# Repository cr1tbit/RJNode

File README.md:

# RJNode

ESP32-C3 Ethernet relay node (2 relays, CH390D Ethernet).

> [!WARNING]
> **This board runs on 230 V AC mains, which can kill.** Mains voltage is present on the
> input terminal, both fuses, the MOV, the AC/DC module primary, the relays and all output
> terminals whenever the board is connected, even with both relays OFF.
>
> - Only a qualified electrician, or someone competent to work on mains, should build, install or service it.
> - Disconnect and isolate the supply, and verify it is dead, before touching the board or the wiring.
> - Never operate it on mains without the enclosure fitted. Do not touch the PCB, USB-C or
>   programming header while mains is connected. For firmware work, power it from USB only, with mains disconnected.
> - This design has **not been certified or safety-tested**. Its AC/DC module
>   (HLK-5M05) gives only about basic insulation; the RJ45 magnetics are an informal second barrier.
>   It is meant for internal or trial use, inside a closed enclosure, behind a circuit breaker.
>
> You build and use this design at your own risk.

## Power rating

**Proposed rating (not yet validated on hardware): 230 V~ 50 Hz, max 250 W per channel, 500 W total.**

| Parameter | Value |
| --- | --- |
| Supply | 230 V AC, 50 Hz (the AC/DC module accepts 85–264 V AC) |
| Load per channel | ≤ 250 W (≈ 1.2 A at PF 0.9) |
| Total input current | ≤ 2.4 A (main fuse: T4A, 1500 A breaking) |
| LED drivers | ≤ 4 per channel, cold-start inrush ≤ 50 A / 250 µs each |
| Outputs | 2 × changeover (NO/NC), neutral passes through. No PE on the PCB; join PE outside the board |
| Insulation class | Class II (no protective earth) |
| Device consumption | ≤ 5 W (5 V / 1 A AC/DC module) |

Notes:

- **The limit is set by the fuse and the inrush, not by the relays or terminals.** The SRD relays are
  10 A parts derated to about 5 A resistive, and the terminals are rated 16 A / 300 V. The main
  fuse sizing and the inrush budget only cover the figures above. Do not fit a larger fuse to
  get more power.
- **Inrush depends on the number of drivers, not on wattage.** Check each LED driver's datasheet
  against the inrush limit. Cheap drivers without an NTC can exceed it.
- **The firmware never switches both relays at the same instant** (≥ 100 ms apart), so the main fuse sees only one channel's inrush at a time.
- **Large motors, compressors and capacitive loads are not covered** by this rating.
- **Still to verify:** a full-load thermal run (terminal, trace and fuse temperatures inside the
  closed enclosure) and an inrush measurement with the real load.

## Repository layout

| Path | Contents |
| --- | --- |
| `RJNode.kicad_*` | KiCad project: schematic, PCB, custom design rules (`.kicad_dru`) |
| `RJNode-schematic.pdf` | Schematic export |
| `tools/` | KiCad helper scripts (net classes + DRU rules, 3D model assignment) |
| `jlcpcb/` | Fabrication output (gerbers, BOM, CPL) |
| `fw/` | PlatformIO / ESP-IDF firmware — see [fw/README.md](fw/README.md) |
| `3d/` | Enclosure CAD, exports and generators — see [3d/README.md](3d/README.md) |

Regenerate the schematic PDF:

```sh
kicad-cli sch export pdf -o RJNode-schematic.pdf RJNode.kicad_sch
```

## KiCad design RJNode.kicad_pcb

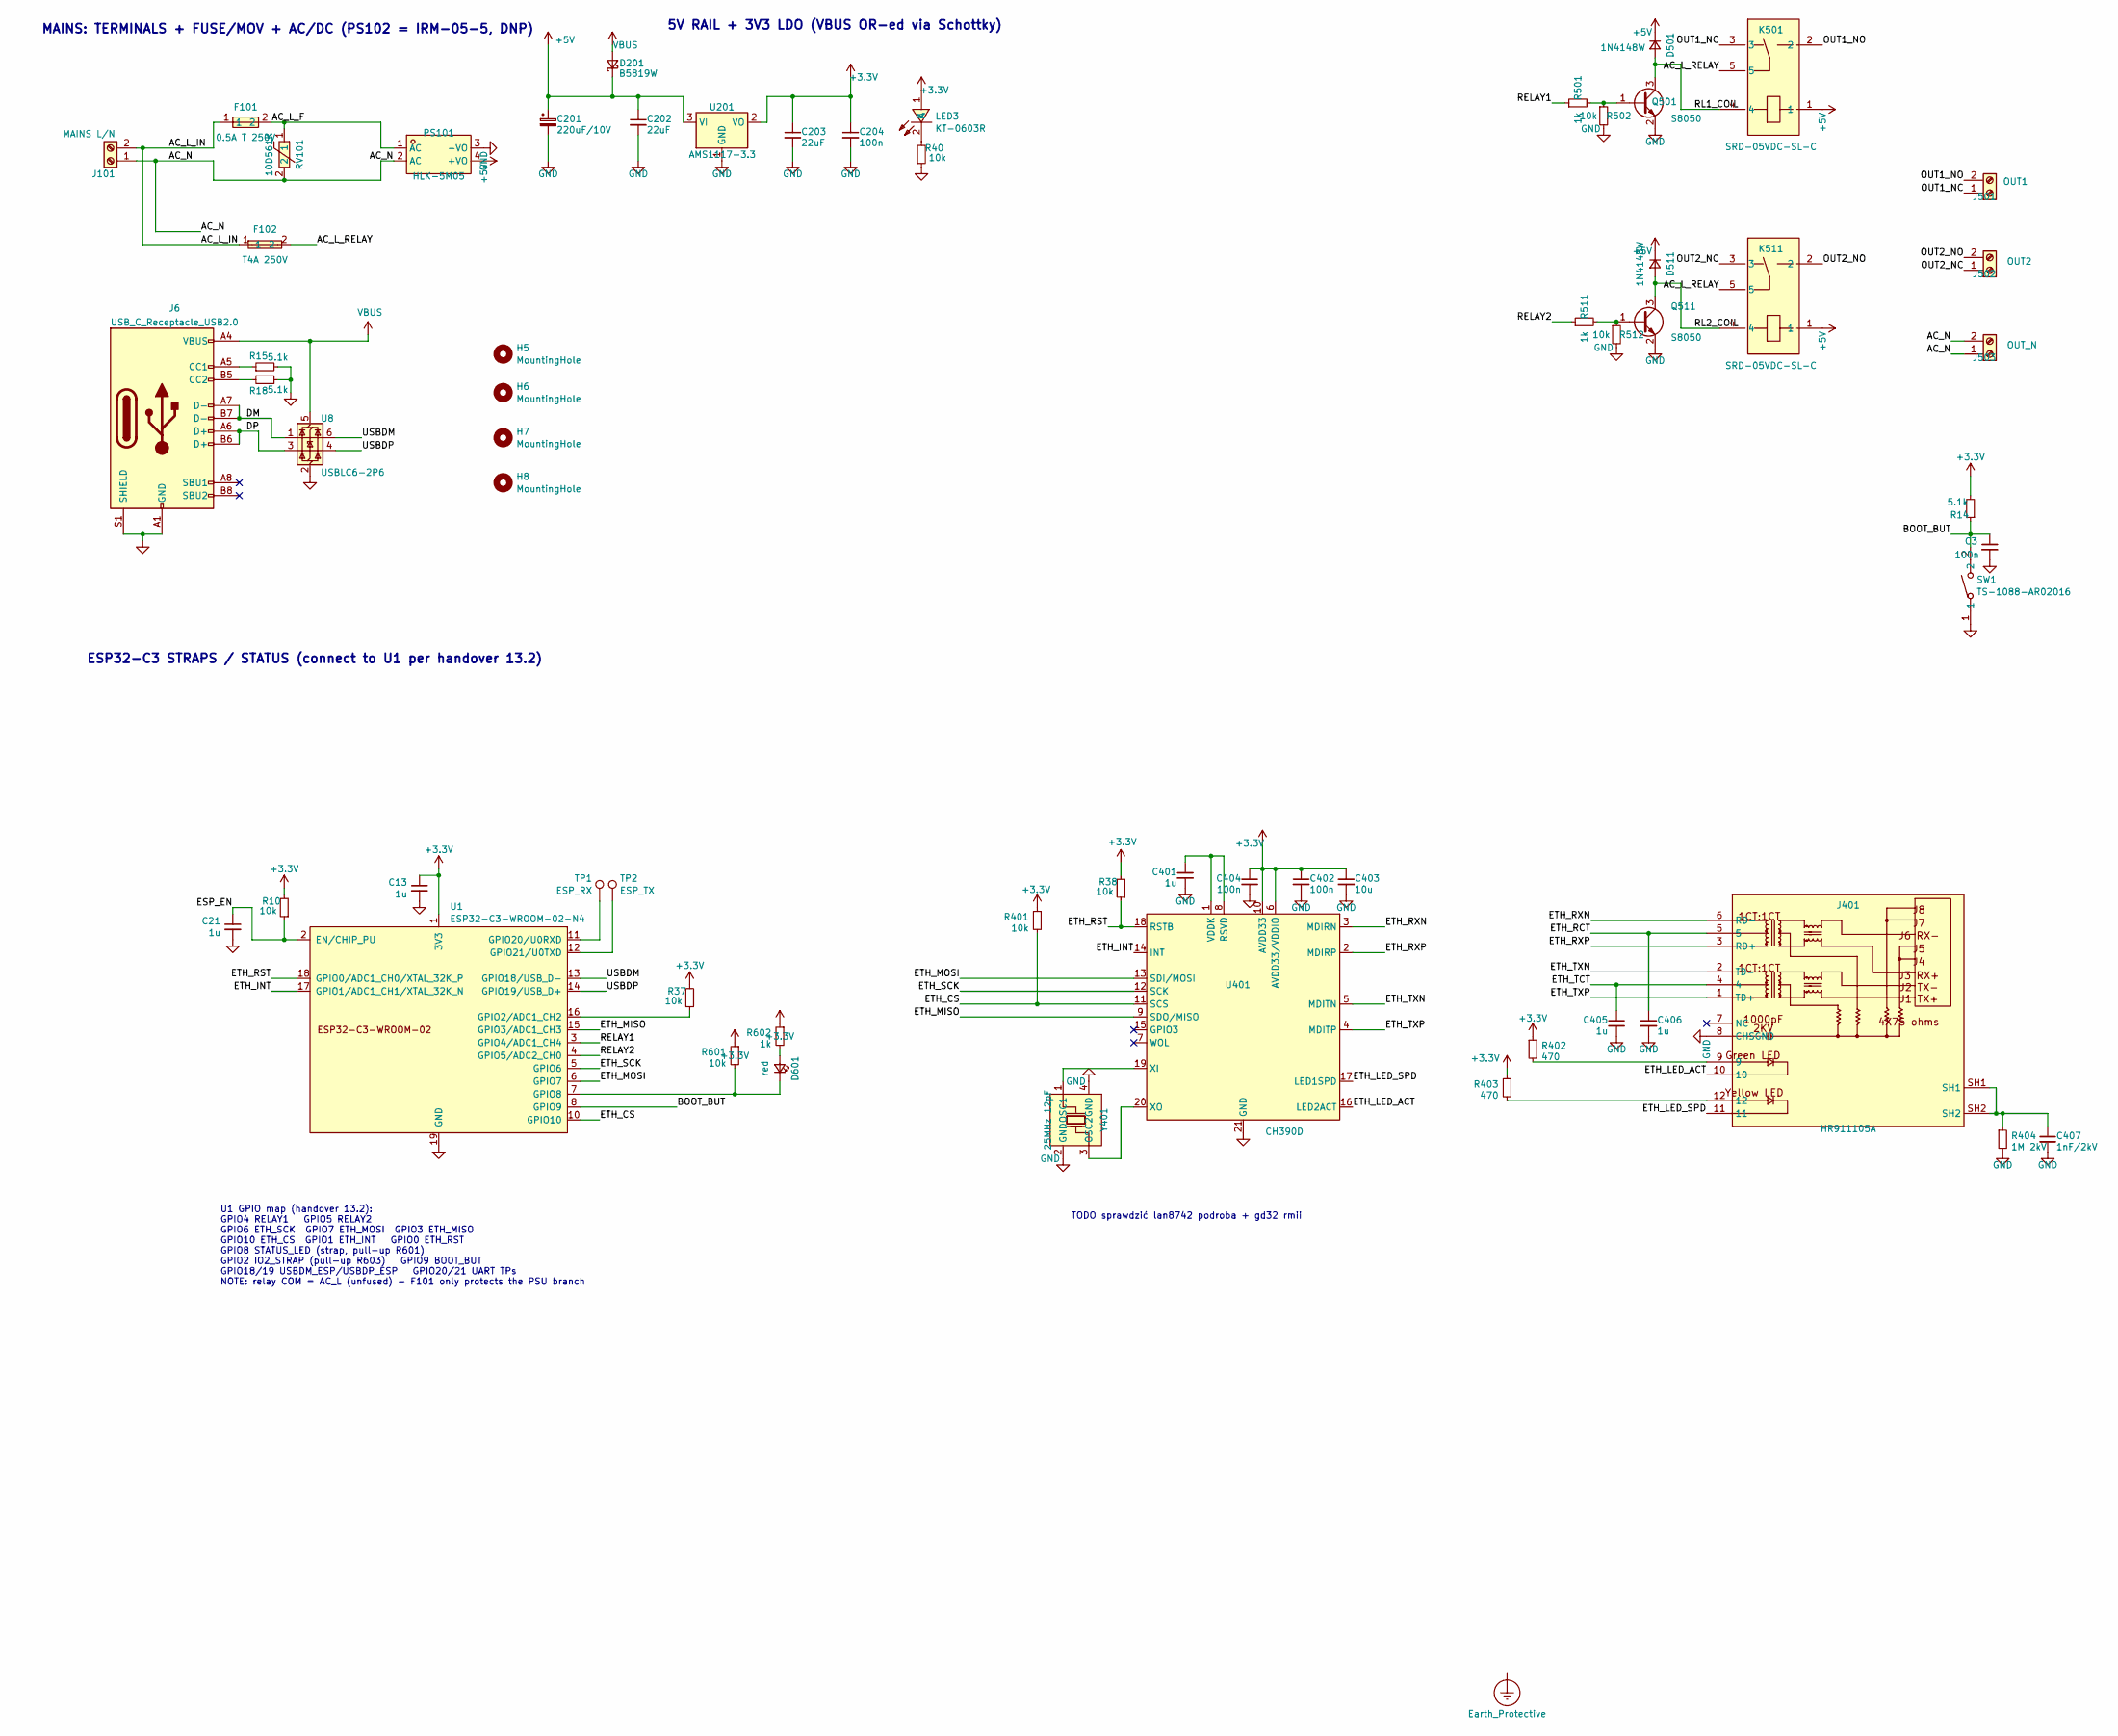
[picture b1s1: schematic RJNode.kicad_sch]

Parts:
C3, C204, C402, C404: 100n; C_0402_1005Metric; LCSC C1525
C13, C21, C401, C405, C406: 1u; C_0402_1005Metric; LCSC C52923
C201: 220uF/10V; CAP-SMD_BD6.3-L6.6-W6.6-FD; LCSC C22383794
C202, C203: 22uF; C_0805_2012Metric; LCSC C45783
C403: 10u; C_0805_2012Metric; LCSC C15850
C407: 1nF/2kV; C_1206_3216Metric; LCSC C9196
D201: B5819W; D_SOD-123; LCSC C8598
D501, D511: 1N4148W; D_SOD-123; LCSC C81598
D601: red; LED_0603_1608Metric; LCSC C2286
F101: 0.5A T 250V; FUSE-TH_L8.5-W4.0-P5.08-D0.6; LCSC C140483
F102: T4A 250V; FUSE-TH_BD5.5-L21.5-P25.50-D0.7; MPN 0215004.MXEP; LCSC C178840
H5, H6, H7, H8: MountingHole; MountingHole_3.2mm_M3
J6: USB_C_Receptacle_USB2.0; USB_C_Receptacle_HRO_TYPE-C-31-M-12_S1; LCSC C165948
J101: MAINS L/N; CONN-TH_DB128V-7.62-2P-GN-S; LCSC C2686074
J401: HR911105A; RJ45-TH_HR911105A; LCSC C12074
J501: OUT1; CONN-TH_DB128V-7.62-2P-GN-S; LCSC C2686074
J502: OUT2; CONN-TH_DB128V-7.62-2P-GN-S; LCSC C2686074
J503: OUT_N; CONN-TH_DB128V-7.62-2P-GN-S; LCSC C2686074
K501, K511: SRD-05VDC-SL-C; RELAY-TH_SRD-XXVDC-XL-C; LCSC C35449
LED3: KT-0603R; LED-SMD_L1.6-W0.8-R-RD; MPN KT-0603R; LCSC C2286
PS101: HLK-5M05; PWRM-TH_HLK-5M05; LCSC C209907
Q501, Q511: S8050; SOT-23; LCSC C2146
R10, R37, R38, R40, R401, R502, R512, R601: 10k; R_0402_1005Metric; LCSC C25744
R14, R15, R18: 5.1k; R_0402_1005Metric; LCSC C25905
R402, R403: 470; R_0402_1005Metric; LCSC C25117
R404: 1M 2kV; R_2010_5025Metric; LCSC C2779367
R501, R511, R602: 1k; R_0402_1005Metric; LCSC C11702
RV101: 10D561K; RES-TH_L9.0-W5.5-P7.50-D0.6-S4.00; LCSC C2839517
SW1: TS-1088-AR02016; SW-SMD_L3.9-W3.0-P4.45; LCSC C720477
TP1: ESP_RX; TestPoint_Pad_D1.0mm
TP2: ESP_TX; TestPoint_Pad_D1.0mm
U1: ESP32-C3-WROOM-02-N4; ESP32-C3-WROOM-02_Via0.3; LCSC C2934560
U8: USBLC6-2P6; SOT-666; LCSC C2827693
U201: AMS1117-3.3; SOT-223-3_TabPin2; LCSC C6186
U401: CH390D; QFN-20_L3.0-W3.0-P0.40-BL-EP1.7; MPN CH390D; LCSC C41380359
Y401: 25MHz 12pF; CRYSTAL-SMD_4P-L3.2-W2.5-BL; LCSC C9006

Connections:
+3.3V: C13.1, C203.1, C204.1, C402.1, C403.1, C404.1, LED3.1 (A), R10.2, R14.2, R37.2, R38.2, R401.1, R402.1, R403.1, R601.1, R602.1, U1.1 (3V3), U201.2 (VO), U401.6 (AVDD33/VDDIO), U401.10 (AVDD33)
+5V: C201.1, C202.1, D201.1 (K), D501.1 (K), D511.1 (K), K501.1, K511.1, PS101.4 (+VO), U201.3 (VI)
/AC_L_F: F101.2, PS101.1 (AC), RV101.1
/AC_L_IN: F101.1, F102.1, J101.2
/AC_L_RELAY: F102.2, K501.5, K511.5
/AC_N: J101.1, J503.1, J503.2, PS101.2 (AC), RV101.2
/BOOT_BUT: C3.1, R14.1, SW1.2, U1.8 (GPIO9)
/DM: J6.A7 (D-), J6.B7 (D-), U8.1 (I/O1)
/DP: J6.A6 (D+), J6.B6 (D+), U8.3 (I/O2)
/ESP_EN: C21.1, R10.1, U1.2 (EN/CHIP_PU)
/ETH_CS: R401.2, U1.10 (GPIO10), U401.11 (SCS)
/ETH_INT: U1.17 (GPIO1/ADC1_CH1/XTAL_32K_N), U401.14 (INT)
/ETH_LED_ACT: J401.10, U401.16 (LED2ACT)
/ETH_LED_SPD: J401.11, U401.17 (LED1SPD)
/ETH_MISO: U1.15 (GPIO3/ADC1_CH3), U401.9 (SDO/MISO)
/ETH_MOSI: U1.6 (GPIO7), U401.13 (SDI/MOSI)
/ETH_RCT: C406.1, J401.5
/ETH_RST: R38.1, U1.18 (GPIO0/ADC1_CH0/XTAL_32K_P), U401.18 (RSTB)
/ETH_RXN: J401.6 (RD-), U401.3 (MDIRN)
/ETH_RXP: J401.3 (RD+), U401.2 (MDIRP)
/ETH_SCK: U1.5 (GPIO6), U401.12 (SCK)
/ETH_TCT: C405.1, J401.4
/ETH_TXN: J401.2 (TD-), U401.5 (MDITN)
/ETH_TXP: J401.1 (TD+), U401.4 (MDITP)
/OUT1_NC: J501.1, K501.3
/OUT1_NO: J501.2, K501.2
/OUT2_NC: J502.1, K511.3
/OUT2_NO: J502.2, K511.2
/RELAY1: R501.1, U1.3 (GPIO4/ADC1_CH4)
/RELAY2: R511.1, U1.4 (GPIO5/ADC2_CH0)
/RL1_COIL: D501.2 (A), K501.4, Q501.3 (C)
/RL2_COIL: D511.2 (A), K511.4, Q511.3 (C)
/USBDM: U1.13 (GPIO18/USB_D-), U8.6 (I/O1)
/USBDP: U1.14 (GPIO19/USB_D+), U8.4 (I/O2)
GND: C3.2, C13.2, C21.2, C201.2, C202.2, C203.2, C204.2, C401.2, C402.2, C403.2, C404.2, C405.2, C406.2, C407.2, J6.A1 (GND), J6.A12 (GND), J6.B1 (GND), J6.B12 (GND), J6.S1 (SHIELD), J401.8 (CHSGND), PS101.3 (-VO), Q501.2 (E), Q511.2 (E), R15.2, R18.2, R40.1, R404.2, R502.2, R512.2, SW1.1, U1.9 (GND), U1.19 (GND), U8.2 (GND), U201.1 (GND), U401.21 (GND), Y401.2 (GND), Y401.4 (GND)
unnamed: C407.1, J401.SH1, J401.SH2, R404.1
unnamed: D601.2 (A), R602.2
unnamed: D601.1 (K), R601.2, U1.7 (GPIO8)
unnamed: J6.A5 (CC1), R15.1
unnamed: J6.B5 (CC2), R18.1
unnamed: J401.9, R402.2
unnamed: J401.12, R403.2
unnamed: LED3.2 (K), R40.2
unnamed: Q501.1 (B), R501.2, R502.1
unnamed: Q511.1 (B), R511.2, R512.1
unnamed: R37.1, U1.16 (GPIO2/ADC1_CH2)
unnamed: TP1.1 (1_1), U1.11 (GPIO20/U0RXD)
unnamed: TP2.1 (1_1), U1.12 (GPIO21/U0TXD)
unnamed: C401.1, U401.1 (VDDK), U401.8 (RSVD)
unnamed: U401.19 (XI), Y401.1 (OSC1)
unnamed: U401.20 (XO), Y401.3 (OSC2)
VBUS: D201.2 (A), J6.A4 (VBUS), J6.A9 (VBUS), J6.B4 (VBUS), J6.B9 (VBUS), U8.5 (VBUS)

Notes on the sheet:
MAINS: TERMINALS + FUSE/MOV + AC/DC (PS102 = IRM-05-5, DNP)
5V RAIL + 3V3 LDO (VBUS OR-ed via Schottky)
TODO sprawdzić lan8742 podroba + gd32 rmii
U1 GPIO map (handover 13.2): GPIO4 RELAY1 GPIO5 RELAY2 GPIO6 ETH_SCK GPIO7 ETH_MOSI GPIO3 ETH_MISO GPIO10 ETH_CS GPIO1 ETH_INT GPIO0 ETH_RST GPIO8 STATUS_LED (strap, pull-up R601) GPIO2 IO2_STRAP (pull-up R603) GPIO9 BOOT_BUT GPIO18/19 USBDM_ESP/USBDP_ESP GPIO20/21 UART TPs NOTE: relay COM = AC_L (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
ESP32-C3 STRAPS / STATUS (connect to U1 per handover 13.2)

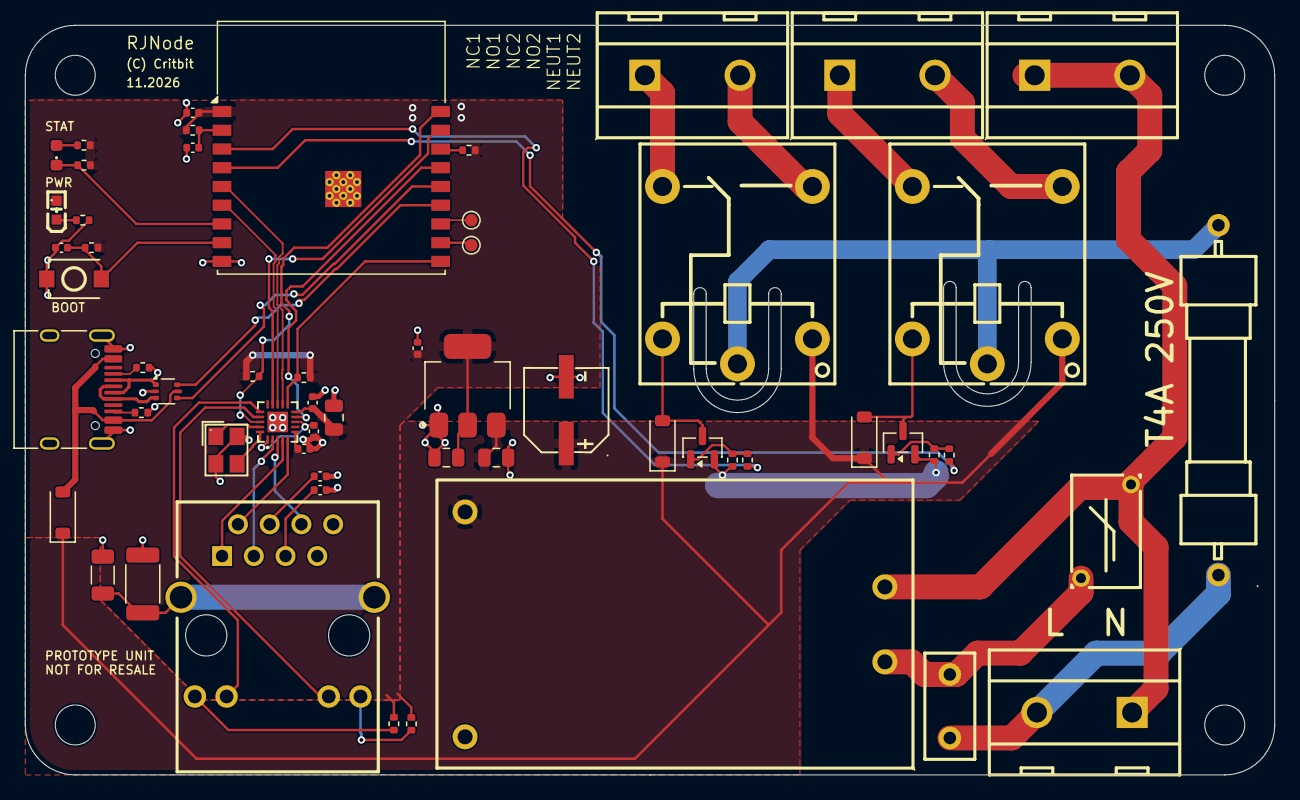
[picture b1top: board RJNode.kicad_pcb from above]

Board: 2 copper layers, 100.0 x 60.0 mm, 62 parts (0 on the bottom side), 52 nets.

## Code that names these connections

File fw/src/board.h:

#pragma once

// RJNode U1, ESP32-C3-WROOM-02-N4; handover.md section 13.2.
#define RELAY1_GPIO 4
#define RELAY2_GPIO 5
#define STATUS_LED_GPIO 8  // Active low; do not drive until after boot straps.
#define ETH_SCK_GPIO 6
#define ETH_MOSI_GPIO 7
#define ETH_MISO_GPIO 3
#define ETH_CS_GPIO 10
#define ETH_INT_GPIO 1
#define ETH_RST_GPIO 0
#define ETH_SPI_CLOCK_HZ (8 * 1000 * 1000)
#define RELAY_ON_GAP_US 100000
